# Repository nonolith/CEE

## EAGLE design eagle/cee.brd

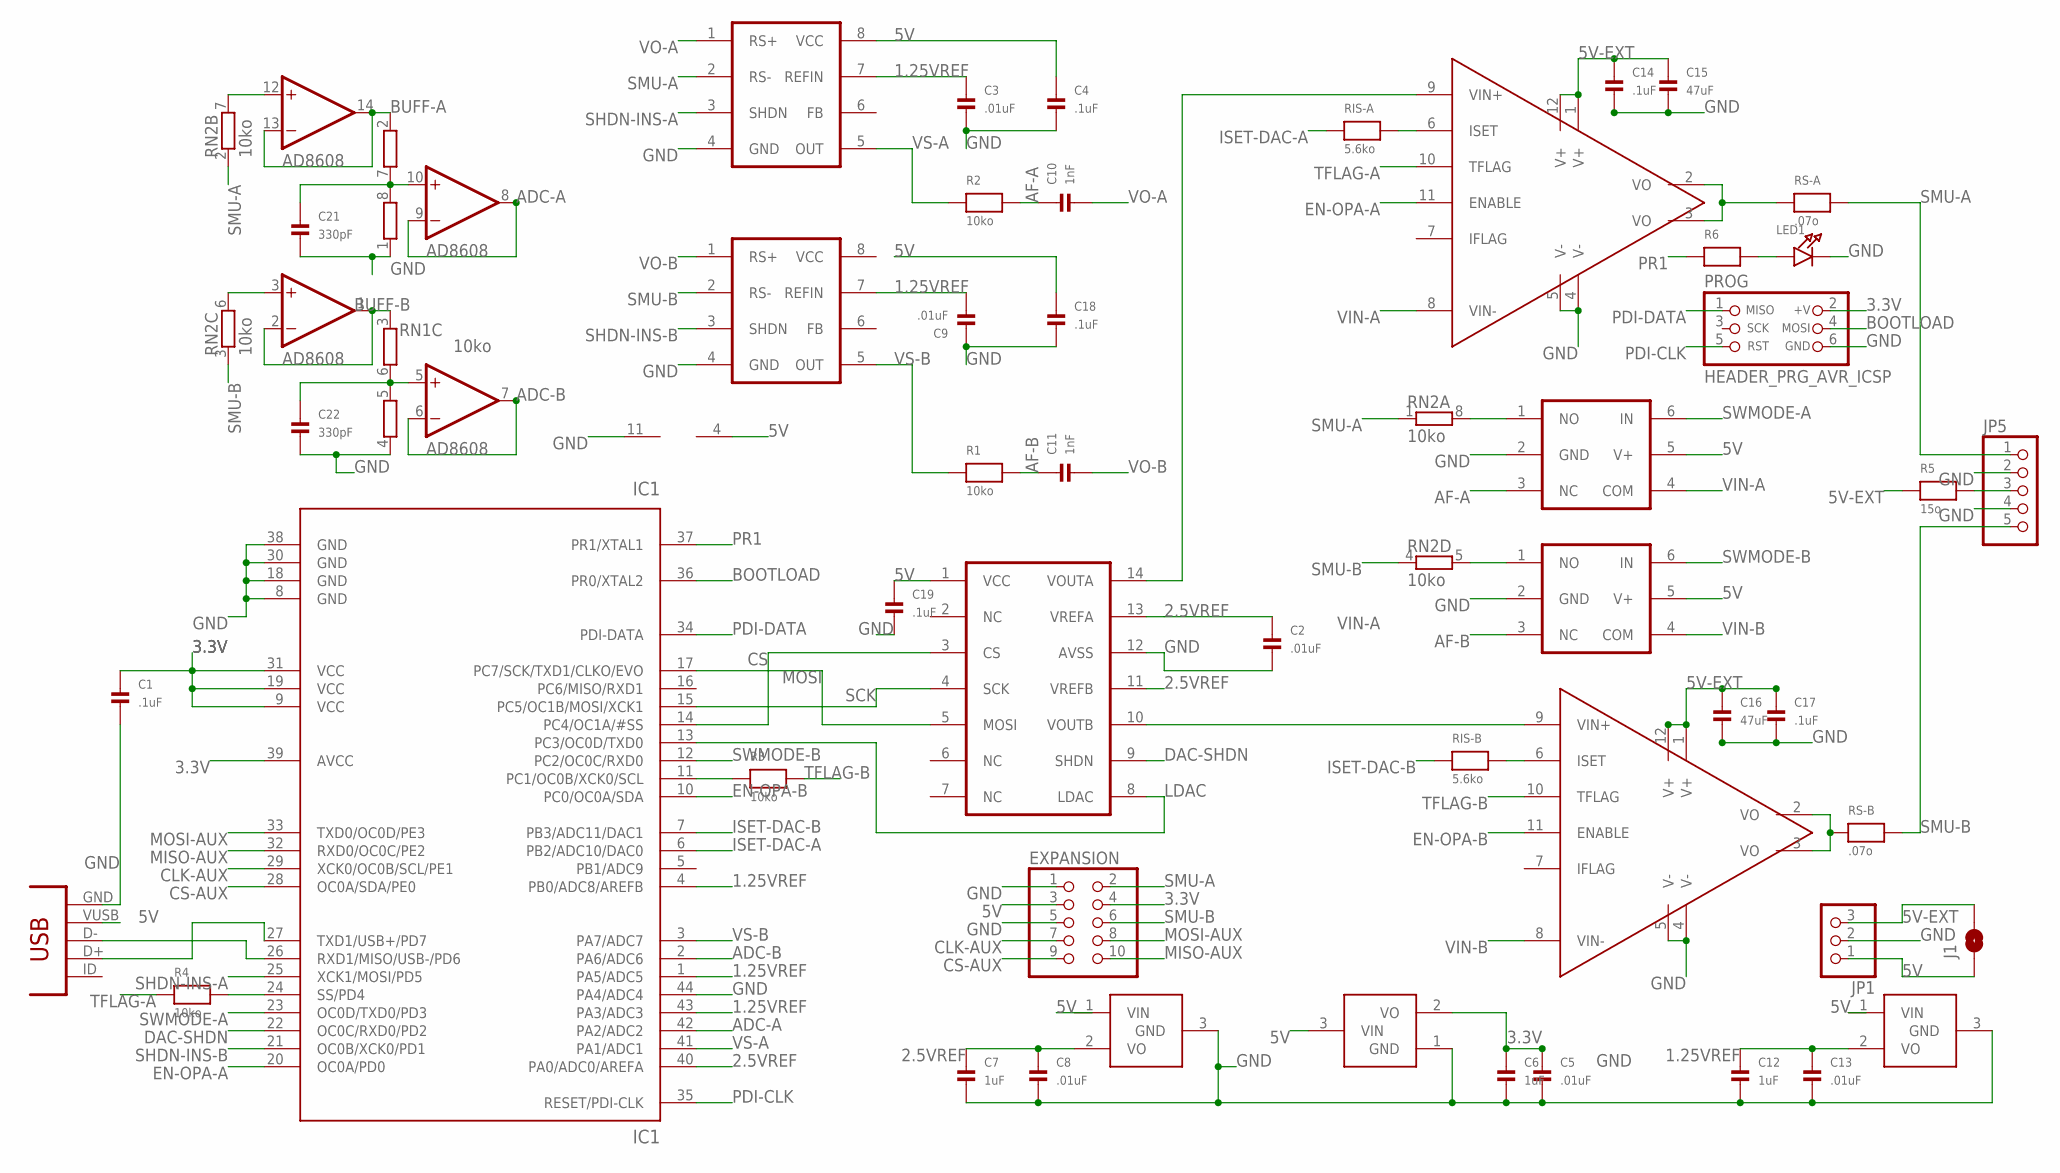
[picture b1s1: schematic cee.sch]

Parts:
1.25REF, 2.5REF: VREF; SOT23-3
3.3VREG: VREG; SOT23-3
C1, C4, C14, C17, C18, C19: .1uF; 0603
C2, C3, C5, C8, C9, C13: .01uF; 0603
C6, C7, C12: 1uF; 0603
C10, C11: 1nF; 0603
C15, C16: 47uF; 1206
C21, C22: 330pF; 0603
CS-A: MAX9919; SO-08
CS-B: MAX9919; SO-08
DAC: MCP4922; SO-14
EXPANSION: HEADER-2X5; 2X05
IC1: IC1; TQFP-44
J1: SOLDERJUMPERNC2; SJ_2S-NOTRACE
JP1: HEADER-1X3ROUND; 1X03_ROUND
JP5: HEADER-1X5ROUND; 1X05_ROUND
LED1: LED0603; CHIPLED_0603
OPA-A: OPA567; QFN-12
OPA-B: OPA567; QFN-12
OPA-C: AD8608; SO-14
PROG: HEADER_PRG_AVR_ICSP; HEADER_PRG_2X03
R1, R2, R3, R4: 10ko; 0603
R5: 15o; 1206
R6: RESISTOR0603; 0603
RIS-A: 5.6ko; 0603
RIS-B: 5.6ko; 0603
RN1, RN2: 10ko; RN8P-4R-CRA06S
RS-A: .07o; 1206
RS-B: .07o; 1206
SW-A: TS5A3157; SOT23-6
SW-B: TS5A3157; SOT23-6
USB1: CON-USB-MINI-BUSB1; CONN_USB_MINI-B

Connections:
1.25VREF: 1.25REF.2 (VO), C3.1, C9.2, C12.1, C13.1, CS-A.7 (REFIN), CS-B.7 (REFIN), IC1.1 (PA5/ADC5), IC1.4 (PB0/ADC8/AREFB), IC1.43 (PA3/ADC3)
2.5VREF: 2.5REF.2 (VO), C2.1, C7.1, C8.1, DAC.11 (VREFB), DAC.13 (VREFA), IC1.40 (PA0/ADC0/AREFA)
3.3V: 3.3VREG.2 (VO), C1.1, C5.1, C6.1, EXPANSION.4, IC1.9 (VCC), IC1.19 (VCC), IC1.31 (VCC), IC1.39 (AVCC), PROG.2 (+V)
5V: 1.25REF.1 (VIN), 2.5REF.1 (VIN), 3.3VREG.3 (VIN), C4.1, C18.1, C19.1, CS-A.8 (VCC), CS-B.8 (VCC), DAC.1 (VCC), EXPANSION.3, J1.1, JP1.1, OPA-C.4 (V+), SW-A.5 (V+), SW-B.5 (V+), USB1.VUSB
5V-EXT: C14.1, C15.1, C16.1, C17.1, J1.2, JP1.3, OPA-A.1 (V+), OPA-A.12 (V+), OPA-B.1 (V+), OPA-B.12 (V+), R5.1
5V-EXT-P: JP5.3, R5.2
ADC-A: IC1.42 (PA2/ADC2), OPA-C.8 (OUT), OPA-C.9 (-IN)
ADC-B: IC1.2 (PA6/ADC6), OPA-C.6 (-IN), OPA-C.7 (OUT)
AF-A: C10.1, R2.2, SW-A.3 (NC)
AF-B: C11.1, R1.2, SW-B.3 (NC)
BOOTLOAD: IC1.36 (PR0/XTAL2), PROG.4 (MOSI)
BUFF-A: OPA-C.13 (-IN), OPA-C.14 (OUT), RN1.2 (1)
BUFF-B: OPA-C.1 (OUT), OPA-C.2 (-IN), RN1.3 (1)
CLK-AUX: EXPANSION.7, IC1.29 (XCK0/OC0B/SCL/PE1)
CS: DAC.3 (CS), IC1.14 (PC4/OC1A/#SS)
CS-AUX: EXPANSION.9, IC1.28 (OC0A/SDA/PE0)
D+: IC1.27 (TXD1/USB+/PD7), USB1.D+
D-: IC1.26 (RXD1/MISO/USB-/PD6), USB1.D-
DAC-SHDN: DAC.9 (SHDN), IC1.22 (OC0C/RXD0/PD2)
EN-OPA-A: IC1.20 (OC0A/PD0), OPA-A.11 (ENABLE)
EN-OPA-B: IC1.10 (PC0/OC0A/SDA), OPA-B.11 (ENABLE)
GND: 1.25REF.3 (GND), 2.5REF.3 (GND), 3.3VREG.1 (GND), C1.2, C2.2, C3.2, C4.2, C5.2, C6.2, C7.2, C8.2, C9.1, C12.2, C13.2, C14.2, C15.2, C16.2, C17.2, C18.2, C19.2, C21.2, C22.2, CS-A.4 (GND), CS-B.4 (GND), DAC.12 (AVSS), EXPANSION.1, EXPANSION.5, IC1.8 (GND), IC1.18 (GND), IC1.30 (GND), IC1.38 (GND), IC1.44 (PA4/ADC4), JP1.2, JP5.2, JP5.4, LED1.C, OPA-A.4 (V-), OPA-A.5 (V-), OPA-B.4 (V-), OPA-B.5 (V-), OPA-C.11 (V-), PROG.6 (GND), RN1.1, RN1.4 (1), SW-A.2 (GND), SW-B.2 (GND), USB1.GND
ISET-A: OPA-A.6 (ISET), RIS-A.2
ISET-B: OPA-B.6 (ISET), RIS-B.2
ISET-DAC-A: IC1.6 (PB2/ADC10/DAC0), RIS-A.1
ISET-DAC-B: IC1.7 (PB3/ADC11/DAC1), RIS-B.1
LDAC: DAC.8 (LDAC), IC1.13 (PC3/OC0D/TXD0)
LEDR: LED1.A, R6.2
MISO-AUX: EXPANSION.10, IC1.32 (RXD0/OC0C/PE2)
MOSI: DAC.5 (MOSI), IC1.17 (PC7/SCK/TXD1/CLKO/EVO)
MOSI-AUX: EXPANSION.8, IC1.33 (TXD0/OC0D/PE3)
unnamed: C21.1, OPA-C.10 (+IN), RN1.7 (2), RN1.8 (2)
unnamed: C22.1, OPA-C.5 (+IN), RN1.5 (2), RN1.6 (2)
PDI-CLK: IC1.35 (RESET/PDI-CLK), PROG.5 (RST)
PDI-DATA: IC1.34 (PDI-DATA), PROG.1 (MISO)
PR1: IC1.37 (PR1/XTAL1), R6.1
SCK: DAC.4 (SCK), IC1.15 (PC5/OC1B/MOSI/XCK1)
SHDN-INS-A: CS-A.3 (SHDN), IC1.25 (XCK1/MOSI/PD5)
SHDN-INS-B: CS-B.3 (SHDN), IC1.21 (OC0B/XCK0/PD1)
SMU-A: CS-A.2 (RS-), EXPANSION.2, JP5.1, RN2.1, RN2.2 (1), RS-A.2
SMU-B: CS-B.2 (RS-), EXPANSION.6, JP5.5, RN2.3 (1), RN2.4 (1), RS-B.2
SMUP-A: OPA-C.12 (+IN), RN2.7 (2)
SMUP-B: OPA-C.3 (+IN), RN2.6 (2)
SMUP-SW-A: RN2.8 (2), SW-A.1 (NO)
SMUP-SW-B: RN2.5 (2), SW-B.1 (NO)
SWMODE-A: IC1.23 (OC0D/TXD0/PD3), SW-A.6 (IN)
SWMODE-B: IC1.12 (PC2/OC0C/RXD0), SW-B.6 (IN)
TFLAG-A: OPA-A.10 (TFLAG), R4.1
TFLAG-B: OPA-B.10 (TFLAG), R3.2
TFLAGP-A: IC1.24 (SS/PD4), R4.2
TFLAGP-B: IC1.11 (PC1/OC0B/XCK0/SCL), R3.1
VIN-A: OPA-A.8 (VIN-), SW-A.4 (COM)
VIN-B: OPA-B.8 (VIN-), SW-B.4 (COM)
VO-A: C10.2, CS-A.1 (RS+), OPA-A.2 (VO), OPA-A.3 (VO), RS-A.1
VO-B: C11.2, CS-B.1 (RS+), OPA-B.2 (VO), OPA-B.3 (VO), RS-B.1
VOUT-A: DAC.14 (VOUTA), OPA-A.9 (VIN+)
VOUT-B: DAC.10 (VOUTB), OPA-B.9 (VIN+)
VS-A: CS-A.5 (OUT), IC1.41 (PA1/ADC1), R2.1
VS-B: CS-B.5 (OUT), IC1.3 (PA7/ADC7), R1.1

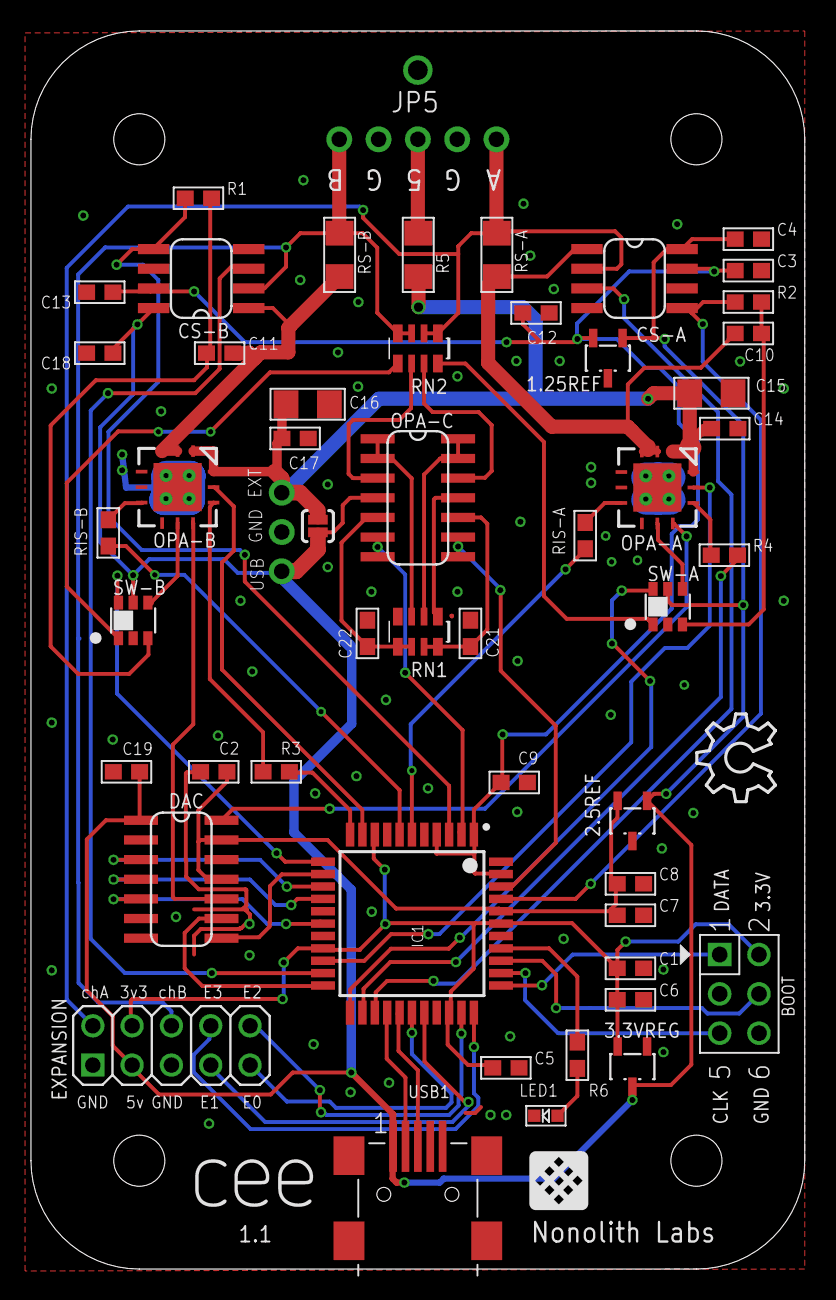
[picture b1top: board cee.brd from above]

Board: 2 copper layers, 50.0 x 80.0 mm, 59 parts (0 on the bottom side), 59 nets.

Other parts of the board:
U$1: OSHW_8X200_NOTEXT
U$2: LOGO_CEE
U$3: LOGO_NONOLITH
U$8, U$9, U$10, U$11: STAND-OFF

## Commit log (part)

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2011-06-30 initial commit of eagle files for schematic test board
2011-06-30 added readme, CC-by-SA license link.
2011-06-30 pesky spelling.
2011-07-02 Fix link in README
2011-07-05 rotated eagle schem
2011-07-05 I know it's binary, but it'll Just Work.
2011-07-05 rm'ed dysfunctional HTML file
2011-07-08 added truth table for one-channel devboard
2011-07-10 added labels to all nets
2011-07-19 extended pads on qfn12/opa567 by .2mm
2011-07-19 adjusted formatting for proper github display
2011-07-20 some several few modifications to the library. renamed/redescribed parts.
2011-07-20 added mcp4922, ad8608, removed testpoints, few other small changes
2011-07-21 more wires and netlabels. missing opamp buffer and vref
2011-07-21 decoupled, vref'ed, vcc'ed
2011-07-21 added pinmappings for TSSOP14 AD8608
2011-07-21 fixed pinout for vreg and vref
2011-07-22 removed old eagle files based on h-bridge switching and lpc1343
2011-07-22 v3/v3.sch
2011-07-22 added iset resistors on opa-a and opa-b
2011-07-22 added resistor values for RIS-A/B
2011-07-22 128 airwires to go...
2011-07-25 added resistor values for INA2332 gainset
2011-07-29 added MAX9919/20, SO-08, and SO-16
2011-07-29 added MAX9919/20
2011-07-29 added ad8606 2chan opamp, reworked schem to reflect recent part decisions
2011-07-29 rm'ed temp files accidentally added to repo
2011-07-29 oops, had an extra 2.5VREF instead of a 1.25VREF
2011-07-29 added power connections to AD8606.
2011-07-29 remove LPC1343 firmware
2011-07-29 update simplified schematic
2011-07-29 Add protection resistors
2011-07-29 removed BOM.pdf in favor of bit.ly/CEEBOM
2011-07-29 added link to BOM in readme.mkd
2011-08-01 Board boundaries and mounting holes
2011-08-03 Ground fill
2011-08-07 more layout, rm'ed gainset from max9919
2011-08-07 Start routing
2011-08-07 more routing
2011-08-07 replaced dual SPDT switch with a pair of single SPDT switches, increasing ease of routing.
2011-08-07 GND and 5V routes
2011-08-08 optimizations and extra caps on the opa567
2011-08-08 Adjust ground planes
2011-08-08 Add to silkscreen, update board images
2011-08-08 12mil ground plane clearance, tented vias
2011-08-09 Header positioning; via tweaks
2011-08-09 sync board to lib
2011-08-09 Rework pins for better layout
2011-08-09 Improve ground plane
2011-08-09 grounding tweaks
2011-08-10 1.25VREF to REFB
2011-08-11 Clean up traces
2011-08-11 Update images
2011-08-12 8mil spacing, more OCD about trace angle
2011-08-12 Split external 5V rail
2011-08-12 MAX9919 decoupling caps
2011-08-13 small board mods; increased trace spacing and width
2011-10-01 Library: fix MCP1700 pinout (new part added)
2011-10-01 Add firmware source
2011-10-01 Refactor: move packetbuffer code to its own set of files.
2011-10-01 Use new USB endpoints API
2011-10-04 changed programmer from jtagmkII to dragon_pdi
2011-10-04 added configSPI function to set up USARTC1 to talk to the MCP4922
2011-10-04 added DAC write function to main.c, include <delay.h> to cee.h
2011-10-04 added writeDAC vrequest as 0xB0
2011-10-04 incremental but important improvements. also, debugging without a working logic analyzer is miserable.
2011-10-05 calling it a night. DAC control is pretty much fail at the moment, but the pieces should be in place
2011-10-05 Add gitignore
2011-10-06 Fix DAC SPI. - Configure 1MHz baud rate - Clear TX complete flag before using it - Mask and pack data correctly
2011-10-06 standardized function naming conventions to camelCase and config/read/writePeripheral
2011-10-06 setting current/voltage is working! :D
2011-10-07 Pull iset low to enable OPA567
2011-10-07 cleaned code, fixed iset function
2011-10-07 broke the 12b pack structure, but added initADC and readADC
2011-10-07 changed the flag
2011-10-08 sequential handling of ADCA.CH0 works - virtual channels were broken
2011-10-08 commented readADC to clarify pin/info mappings
2011-10-08 added/rehashed the prefunction comments
2011-10-09 Add command to enter bootloader
2011-10-10 added update.py, a firmware update script that calls the CEE vendor request to reset into bootloader and calls usb/bootloader/flash.py
2011-10-10 changed ADC to differential mode for great justice
2011-10-10 added offset removal function for better accuracy. switched ADC ground from external to internal for higher precision
2011-10-12 replaced busyloop ADC code with dysfunctional freerun code
2011-10-13 fixed sign error
2011-10-14 updated comments on initADC and readADC
2011-10-14 added DAC in SOIC
2011-10-15 centered the package QFN12 and updated the v3.brd and v3.sch accordingly
2011-10-16 reworked several traces - need to fix SMU-B to ADC-B and DAC routing. can't wait for vdiffs enabled via .brd/.sch as xml files...
2011-10-16 Route SOIC DAC
2011-10-16 fully routed - extensive fixes of analog frontend and voltage regulators. TODO: silkscreen, DRC
2011-10-17 added RC series circuit providing a higher-bw path in series with MAX9919
2011-10-17 fixed DRC except for opa567 errors and 'drill size' errors.
2011-10-17 Clean up minor zigzags in traces
2011-10-17 Clean up traces and silkscreen
2011-10-17 moved programming header from awkward five-pin to kosher six-pin (2x3)
2011-10-17 updated board and library with [hopefully] visible silkscreen dot indicating switch orientation
2011-10-17 moved parts and polygons to have a 50 by 80 profile
2011-10-18 added protection resistors on TFLAGs and on switch inputs
2011-10-19 Align traces, clean up. library: remove holes from USB footprint
2011-10-19 Add decoupling caps on 5v rail for DAC and opamp
2011-10-19 Add silkscreen labels for expansion header
2011-10-19 Add logos
2011-10-19 added explicit comments to describe packet-related functions
2011-10-19 first pass at getting bulk transfers working in xmega firmware; changed TCC0 from 4MHz to 1MHz for easy math
2011-10-19 Working ADC IN streaming
2011-10-19 added 1x2 .1" header as testpoints on D+ and D- giving us a push-and-play test connection
2011-10-25 added lowpass cap on voltage divider for SMUA/B sense
2011-10-25 place capacitors symmetrically
2011-10-25 renamed some packages to match convention, added ADXL3XX, cleaned up part variants for VREF et al
2011-10-25 backporting changes to nonolith.lbr made in the thermowut branch
2011-10-27 s/packet/inPacket/ to clear up variable naming conventions when dealing with bidirectional packets
2011-10-27 s/sampleIndex/inSampleIndex/ to clear up variable naming conventions when dealing with bidirectional packets
2011-10-28 added hardware.h to abstract implementation-specific pinmappings away
2011-10-28 initial commit of untested asynch bidirectional code
2011-10-28 cleaned up ordering of header files, moved MCP4922 flag definitions to hardware.h
2011-10-28 moved variable definitions to the top, removed calls to the inline functions with their literals
2011-10-29 Streaming working with interrupts
2011-10-29 Increase SPI clock
2011-10-29 SPI output looks ok...at 10ksps
2011-10-30 optimize
2011-10-30 DAC SPI: clear TXCIF after enabling TXC to avoid race condition
2011-11-08 cleanup cleanup
2011-11-08 added values to a few components, rm'ed nonolith.lbr
2011-11-10 added early-stage support for the xmega's internal gain
2011-11-11 Add case design
2011-11-15 cleaned up gainset *again*
2011-11-17 went from ad8606 to ad8608 for full input buffering
2011-11-17 cleanup.
2011-11-17 further cleanup of schematic - assigned values to parts, changed linewidth, added labels.
2011-11-17 standardized value formats
2011-11-17 added values for antialiasing caps, added second resistor network for protection
2011-11-17 Seeed DRC checks out
2011-11-18 moved 5V supply to center pin on main output header, included 1206 pad for protection resistor, cleaned up silkscreen
2011-11-19 clean up / organize schematics and export binaries
2011-11-19 that was almost bad. had a ground via going through a power trace...
2011-11-19 clean up routing
2011-11-19 add 200mA current limit reflecting shippable product
2011-11-20 Position header such that it lines up with the edge of the case. Fix silkscreen.
2011-11-20 Rotate silkscreen on output pins
2011-11-20 cleaned up silkscreen with readable part numbers
2011-11-20 tweak label positioning
2011-11-20 added binaries of the board
2011-11-20 Move RN1 down for easier soldering
2011-11-22 fixed hole dimensions, moved from svg w/ inkscape + sodipodi namespaces to 'plain' svg
2011-11-23 fixed(?) hole spacing
2011-11-23 Add dimensioned CEE case. Save ceeCase.svg as standard svg
2011-11-23 updated to match d22de80 in Nonolith-Eagle-Library
2011-11-27 cleaned up variable & function names, removed debugging calls to PORTE
2011-11-27 overcommented startWriteDAC / DRE_vect / TXC_vect, possibly fixed DRE_vect
2011-11-27 added silkscreen for JP5 / output header
2011-11-27 commented vendor requests
2011-11-30 Add notch for USB cable clearance
2011-12-01 added values for R5, C21, and C22
2011-12-03 fixed dual-channel DAC code for ISET
2011-12-03 Fix IN_sample packing (readADC).
    The ADC sign-extends negative numbers, so an &0x0f is necessary
    when packing as 12b.
2011-12-05 added fids by OSHW logo and output header
2011-12-05 added second GND connection to expansion header, replacing NC with something useful
2011-12-06 added fixed cee.py
2011-12-06 put python library in root folder
2011-12-06 removed simplified schematic. it needs to be rebuilt to update and needs to be designed to actually explain things to people who don't know the characteristics of an ideal volt/amp meter
2011-12-09 moar comments
2011-12-10 reworked traces and vias central to miniusb connector
2011-12-10 uh... not sure how that got there
2011-12-14 added vReq for ISet -> 0x15, wIndex -> 0x0A, 0x0B, wValue -> DAC
2011-12-20 s/1.0 RC3/1.0/
2011-12-28 Add vendor request to reset all buffers and start sampling
2011-12-28 Disable outputs when not capturing
2012-01-04 add LED behavior - blink 50ms on power, then indicate USB bulk streaming
2012-01-11 renamed eagle files
2012-01-12 bootload target in makefile
2012-01-12 Fix update.py
2012-01-13 Update usb/
2012-01-15 firmware: Vendor request for getting version information
2012-01-20 Remove firmware (Moved to a separate git repository @ https://github.com/nonolith/cee-firmware )
2012-01-20 Add 'see also' links to other repos in readme.
2012-01-24 added production BOM for V1.0
2012-02-08 major schematic cleanup - sane sheet divisions, clean up extraneous connections
2012-02-08 killed fake fids
2012-02-08 fully routed; passes DRC; cleaned up older traces a bit
2012-02-10 cleaned up page 1 of schematic
2012-03-06 renamed to clarify functionality
2012-03-19 no longer have noncommercial use as a remix stipulation
2012-11-10 Beginning of v2: Reroute xmega side
2012-11-11 Move output header 1mm inward so it doesn't go beyond acrylic.
2012-11-12 more routing, moved some stuff around
2012-11-16 did I winzorz
2012-11-16 fix drc error - tolerance on trace running under resistors
2012-11-16 pulldown resistor, chanB as input, moved capacitors, updated sc70, cleaned routing
2012-11-16 Clean up around DAC
2012-11-16 Clean up, route digital lines
2012-11-16 Tweak 3v3 plane to keep GND connection
2012-11-16 Update library (SC70 and QFN)
2012-11-16 Update OPA567
2013-01-15 rotate 90deg
2013-01-26 significantly revised schematic including feedback compensation loooooops and mcp6n11
2013-01-26 move SIMV minor loop from '567 to around CSA for functionality clarification
2013-01-26 cleaned up the routing of the CSA, for some definitions of clean.
2013-01-27 Clean up MCP6N11 routing * Move it to the right place * Fix 2.5V bypassing * Fix OPA567 power
2013-01-27 Connect CSA EN pin
2013-01-27 Rename VOUT-B -> ADCREF
2013-01-27 Reorganize schematic
2013-01-27 More cleanup and reorganization
2013-01-27 Remove old binaries.
2013-01-27 Swap position of VEXT and SJ1
2013-01-27 Use LME49726 for current-limited 5V.
2013-01-28 Tweaks: GND plane around CSA, etc.
2013-01-28 add junctions, leading zeroes, drop dangling 'o's
2013-01-28 Add series resistor with compensation capacitor.
2013-01-28 Clean up ISP header labels
2013-01-30 Update RGB LED with +/-
2013-01-30 Tweaks: PLCC dot in tstop, move via
2013-03-12 initial routing of v2rc1 with ina213
2013-05-14 Label v2RC1 (manufactured with 'beta 2' text)
2013-05-31 Add Bill of Materials (As manufactured on V1.0)
2013-06-05 Update silkscreen: * Version 1.1 * Reposition logos * Remove fiducials
2013-06-05 Add more GND plane stitching
